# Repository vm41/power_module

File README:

-------------------------------------------------------
This is new branch c122017 created from the master branch
Migration of measure.py to more object oriented form.

DO NOT DELETE "2016_everything.zip"
That is not a backup!
----------------------------------
Documentations for selecting the hardware and instruments can be found in "doc"
Basic test scripts can be found in i2c-test

measure.py is the code to run on the drone, to measure motors currents, as well as 
receiving information from the agent, and recording them in log files.

constant.py is a configuration file imported in measure.py

tcp_client.py is a test code to run and act as the agent to send some 
commands to the measure.py manually.

graphs/
All graph related scripts, the ones in 2016 are not necessarily kept anymore, be careful.

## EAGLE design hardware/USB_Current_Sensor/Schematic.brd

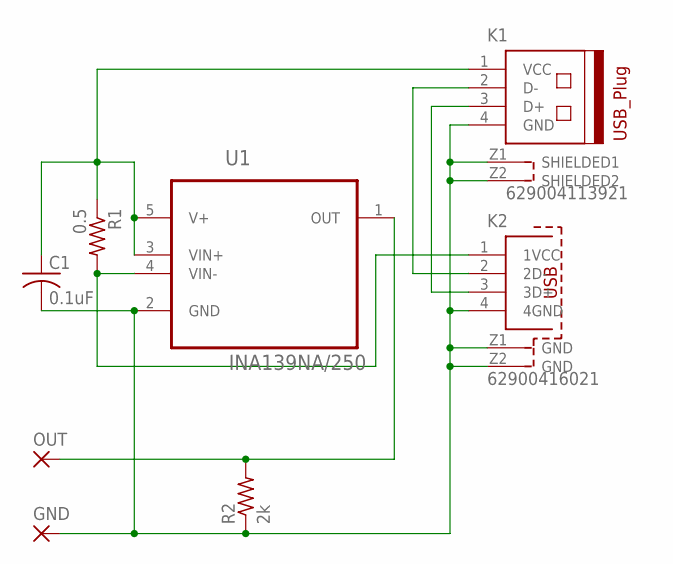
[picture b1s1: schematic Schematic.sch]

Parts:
C1: 0.1uF; C1808
GND: 2,54/1,0
K1: 629004113921
K2: 62900416021
OUT: 2,54/1,0
R1: 0.5; R1206
R2: 2k; R1206
U1: INA139NA/250; SOT95P280X145-5N

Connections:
unnamed: C1.2, GND.1, K1.4 (GND), K1.Z1 (SHIELDED1), K1.Z2 (SHIELDED2), K2.4 (4GND), K2.Z1 (GND), K2.Z2 (GND), R2.1, U1.2 (GND)
unnamed: K1.3 (D+), K2.3 (3D+)
unnamed: K1.2 (D-), K2.2 (2D-)
unnamed: C1.1, K1.1 (VCC), R1.1, U1.3 (VIN+), U1.5 (V+)
unnamed: OUT.1, R2.2, U1.1 (OUT)
unnamed: K2.1 (1VCC), R1.2, U1.4 (VIN-)

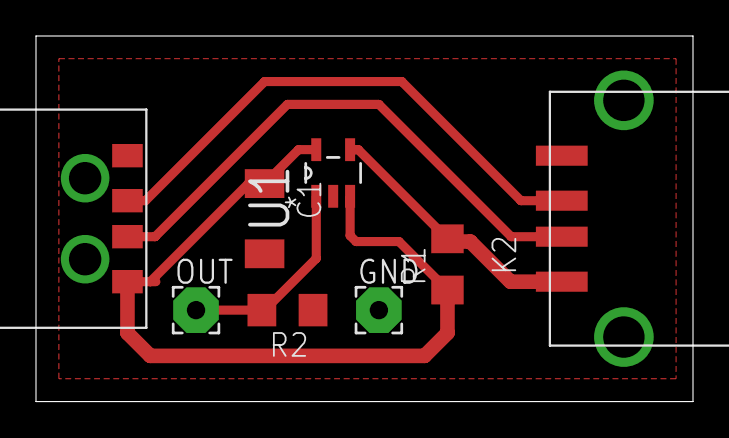
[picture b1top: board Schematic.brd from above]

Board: 2 copper layers, 36.5 x 20.3 mm, 8 parts (0 on the bottom side), 6 nets.

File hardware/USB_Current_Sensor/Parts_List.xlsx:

Number of Boards: |  | 3
Component |  | Quantity (per Board) |  | Quantity (Total) |  | Part Number |  | Price (per Part) |  | Price (Total) | Part Link
Current transducer |  | 1 |  | 3 |  | INA139NA/250 |  | 2 |  | 6 | digikey
0.5ohm resistor |  | 1 |  | 3 |  | CSR1206FTR500 |  | 0.42 |  | 1.26 | digikey
2kohm resistor |  | 1 |  | 3 |  | TNPW12062K00BEEA |  | 0.72 |  | 2.16 | digikey
0.1uF capacitor |  | 1 |  | 3 |  | VJ1808Y104KXCAT |  | 0.75 |  | 2.25 | digikey
USB A Male |  | 1 |  | 3 |  | "629004113921" |  | 2.21 |  | 6.63 | digikey
USB A Female |  | 1 |  | 3 |  | "62900416021" |  | 2.36 |  | 7.08 | digikey
 |  |  |  |  |  |  |  | Price (per Board) |  | Price (Total boards)
 |  |  |  |  |  |  |  | 8.4599999999999991 |  | 25.379999999999995

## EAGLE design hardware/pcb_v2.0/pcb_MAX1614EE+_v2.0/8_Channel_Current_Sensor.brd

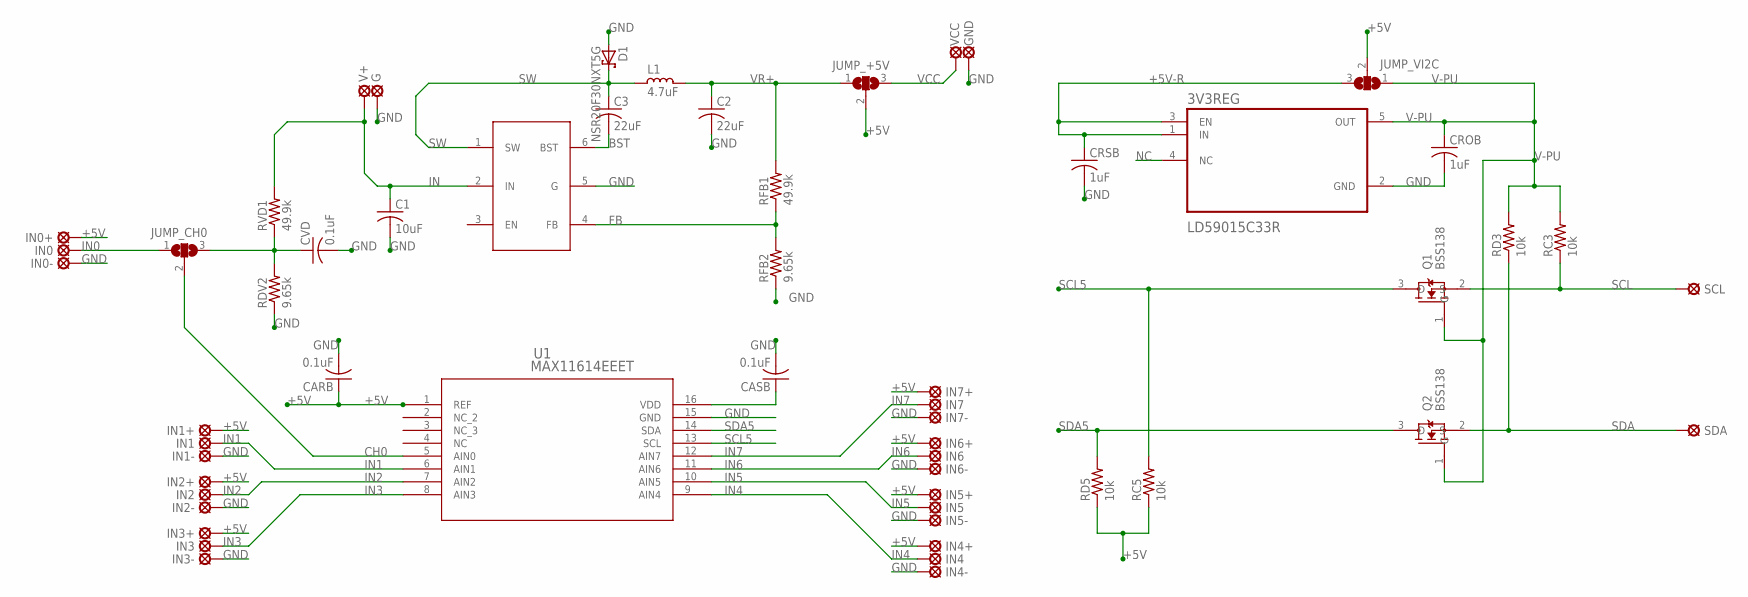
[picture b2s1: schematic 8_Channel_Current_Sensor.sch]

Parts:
3V3REG: LD59015C33R; SOT65P210X110-5N
5VBUCK: ACT4088US-T; SOT236
C1: 10uF; C0603K
C2, C3: 22uF; C0603K
CARB: 0.1uF; C0603
CASB: 0.1uF; C0603
CROB: 1uF; C0603
CRSB: 1uF; C0603
CVD: 0.1uF; C0603K
D1: NSR20F30NXT5G; C0603K
G: LSP10
GND: LSP10
IN0, IN0+, IN0-, IN1, IN1+, IN1-, IN2, IN2+, IN2-, IN3, IN3+, IN3-, IN4, IN4+, IN4-, IN5, IN5+, IN5-, IN6, IN6+, IN6-, IN7, IN7+, IN7-: LSP10
JUMP_+5V: SJ2W; SJ_2
JUMP_CH0: SJ2W; SJ_2
JUMP_VI2C: SJ2W; SJ_2
L1: 4.7uF; PM1008
Q1, Q2: BSS138; SOT95P240X120-3N
RC3, RC5: 10k; R0603
RD3, RD5: 10k; R0603
RDV2: 9.65k; R0603
RFB1: 49.9k; R0603
RFB2: 9.65k; R0603
RVD1: 49.9k; R0603
SCL: LSP10
SDA: LSP10
U1: MAX11614EEET; 21-0055H_16
V+: LSP10
VCC: LSP10

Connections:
+5V: CARB.1, CASB.1, IN0+.MP, IN1+.MP, IN2+.MP, IN3+.MP, IN4+.MP, IN5+.MP, IN6+.MP, IN7+.MP, JUMP_+5V.2, JUMP_VI2C.2, RC5.1, RD5.1, U1.1 (REF), U1.16 (VDD)
+5V-R: 3V3REG.1 (IN), 3V3REG.3 (EN), CRSB.1, JUMP_VI2C.3
BST: 5VBUCK.6 (BST), C3.2
CH0: JUMP_CH0.2, U1.5 (AIN0)
FB: 5VBUCK.4 (FB), RFB1.1, RFB2.2
GND: 3V3REG.2 (GND), 5VBUCK.5 (G), C1.2, C2.2, CARB.2, CASB.2, CROB.2, CRSB.2, CVD.2, D1.1 (A), G.MP, GND.MP, IN0-.MP, IN1-.MP, IN2-.MP, IN3-.MP, IN4-.MP, IN5-.MP, IN6-.MP, IN7-.MP, RDV2.1, RFB2.1, U1.15 (GND)
IN: 5VBUCK.2 (IN), C1.1, RVD1.2, V+.MP
IN0: IN0.MP, JUMP_CH0.1
IN1: IN1.MP, U1.6 (AIN1)
IN2: IN2.MP, U1.7 (AIN2)
IN3: IN3.MP, U1.8 (AIN3)
IN4: IN4.MP, U1.9 (AIN4)
IN5: IN5.MP, U1.10 (AIN5)
IN6: IN6.MP, U1.11 (AIN6)
IN7: IN7.MP, U1.12 (AIN7)
NC: 3V3REG.4 (NC)
SCL: Q1.2 (S), RC3.1, SCL.MP
SCL5: Q1.3 (D), RC5.2, U1.13 (SCL)
SDA: Q2.2 (S), RD3.1, SDA.MP
SDA5: Q2.3 (D), RD5.2, U1.14 (SDA)
SW: 5VBUCK.1 (SW), C3.1, D1.2 (C), L1.2
V-PU: 3V3REG.5 (OUT), CROB.1, JUMP_VI2C.1, Q1.1 (G), Q2.1 (G), RC3.2, RD3.2
VCC: JUMP_+5V.3, VCC.MP
VD: CVD.1, JUMP_CH0.3, RDV2.2, RVD1.1
VR+: C2.1, JUMP_+5V.1, L1.1, RFB1.2

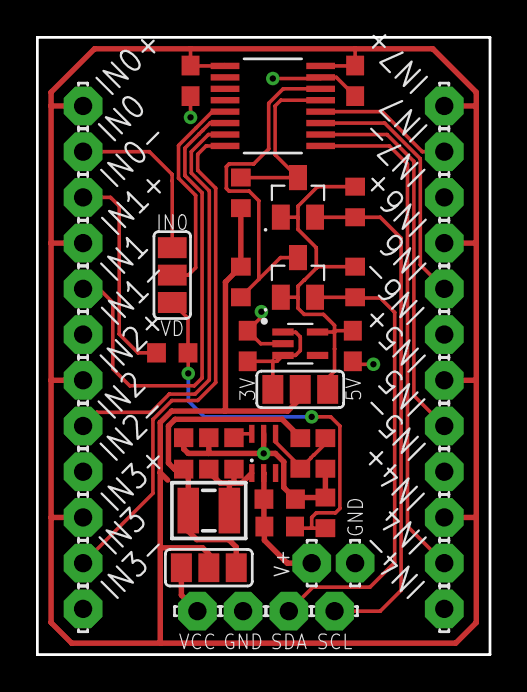
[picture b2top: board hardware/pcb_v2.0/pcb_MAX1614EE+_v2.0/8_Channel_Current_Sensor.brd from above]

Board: 2 copper layers, 25.1 x 34.3 mm, 56 parts (0 on the bottom side), 24 nets.

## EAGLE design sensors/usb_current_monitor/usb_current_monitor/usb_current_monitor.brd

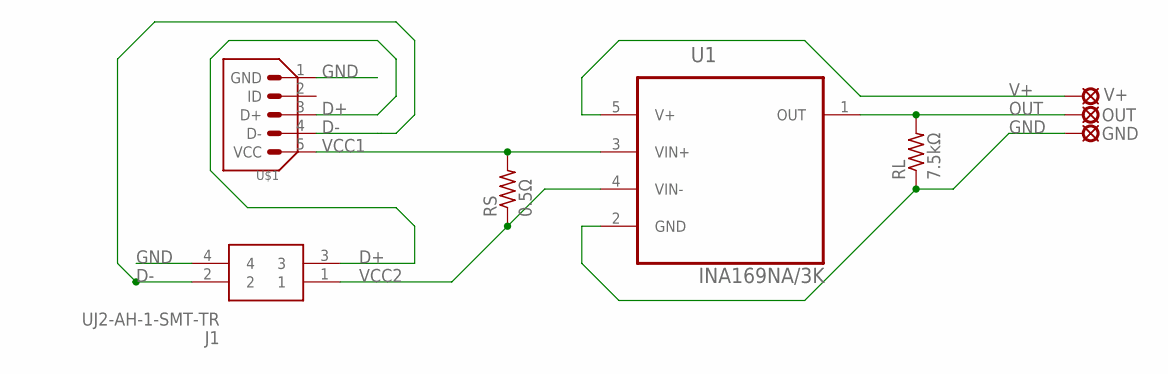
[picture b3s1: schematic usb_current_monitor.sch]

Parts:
GND: LSP10
J1: UJ2-AH-1-SMT-TR
OUT: LSP10
RL: 7.5kΩ; R0603
RS: 0.5Ω; R0603
U1: INA169NA/3K; SOT95P280X145-5N
U$1: ZX62R-B-5P
V+: LSP10

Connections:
D+: J1.3, U$1.3 (D+)
D-: J1.2, U$1.4 (D-)
GND: GND.MP, J1.4, RL.1, U1.2 (GND), U$1.1 (GND)
OUT: OUT.MP, RL.2, U1.1 (OUT)
V+: U1.5 (V+), V+.MP
VCC1: RS.2, U1.3 (VIN+), U$1.5 (VCC)
VCC2: J1.1, RS.1, U1.4 (VIN-)

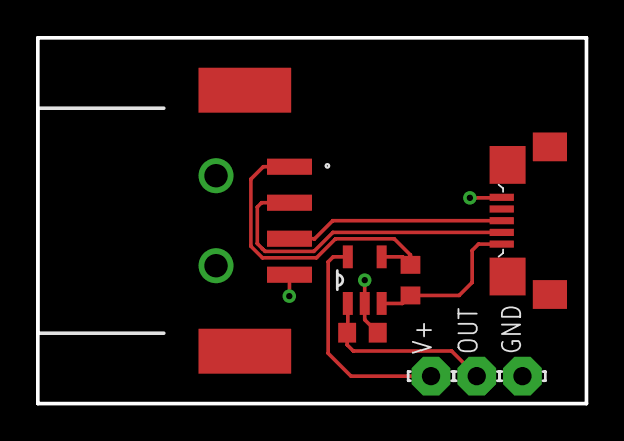
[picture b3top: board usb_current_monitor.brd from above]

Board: 2 copper layers, 30.5 x 20.3 mm, 8 parts (0 on the bottom side), 7 nets.

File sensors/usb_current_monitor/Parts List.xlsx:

No of Boards (mult of 3) | 3
Part | Part No | Quanity | Ext Quantity | Cost | Ext. Cost | Link
Shunt Monitor | INA169NA/3K | 1 | 3 | 2.21 | 6.63 | mouser
Micro USB Connector | ZX62R-B-5P(30) | 1 | 3 | 0.93 | 2.79 | mouser
USB Type A Connector | UJ2-AH-1-SMT-TR | 1 | 3 | 1.1599999999999999 | 3.4799999999999995 | mouser
0.5Ω 0805 Shunt Resistor | LRCS0805-0R5FT5 | 1 | 3 | 0.17 | 0.51 | mouser
7.5kΩ 0805 Load Resistor | ERJ-PB6B7501V | 1 | 3 | 0.57999999999999996 | 1.7399999999999998 | mouser
Optional Headers - Ignore for now |  | 0 | 0 | 0 | 0
Signal Header Female | 505567-0371 | 0 | 0 | 0.73 | 0 | mouser
Signal Header Male | 505565-0301 | 0 | 0 | 0.25 | 0 | mouser
 |  |  | Total Cost: |  | 15.149999999999999

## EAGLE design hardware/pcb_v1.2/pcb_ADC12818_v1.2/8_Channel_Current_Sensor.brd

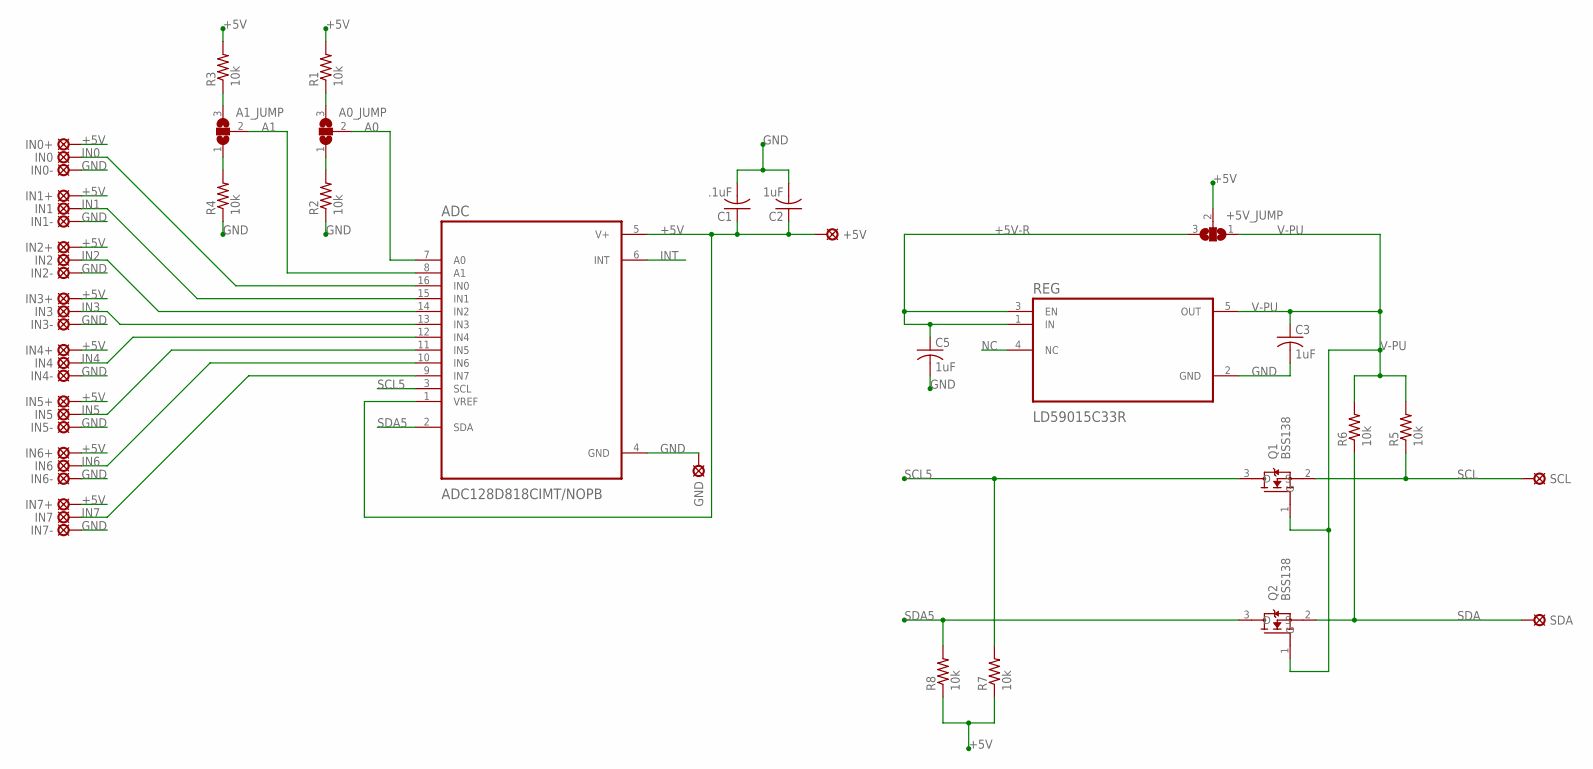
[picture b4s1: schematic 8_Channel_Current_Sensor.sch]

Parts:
+5V: LSP10
+5V_JUMP: SJ2W; SJ_2
A0_JUMP, A1_JUMP: SJ2W; SJ_2
ADC: ADC128D818CIMT/NOPB; SOP65P640X120-16N
C1: .1uF; C0603
C2, C3, C5: 1uF; C0603
GND: LSP10
IN0, IN0+, IN0-, IN1, IN1+, IN1-, IN2, IN2+, IN2-, IN3, IN3+, IN3-, IN4, IN4+, IN4-, IN5, IN5+, IN5-, IN6, IN6+, IN6-, IN7, IN7+, IN7-: LSP10
Q1, Q2: BSS138; SOT95P240X120-3N
R1, R2, R3, R4, R5, R6, R7, R8: 10k; R0603
REG: LD59015C33R; SOT65P210X110-5N
SCL: LSP10
SDA: LSP10

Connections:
+5V: +5V.MP, +5V_JUMP.2, ADC.1 (VREF), ADC.5 (V+), C1.1, C2.1, IN0+.MP, IN1+.MP, IN2+.MP, IN3+.MP, IN4+.MP, IN5+.MP, IN6+.MP, IN7+.MP, R1.2, R3.2, R7.1, R8.1
+5V-R: +5V_JUMP.3, C5.1, REG.1 (IN), REG.3 (EN)
A0: A0_JUMP.2, ADC.7 (A0)
A1: A1_JUMP.2, ADC.8 (A1)
GND: ADC.4 (GND), C1.2, C2.2, C3.2, C5.2, GND.MP, IN0-.MP, IN1-.MP, IN2-.MP, IN3-.MP, IN4-.MP, IN5-.MP, IN6-.MP, IN7-.MP, R2.1, R4.1, REG.2 (GND)
IN0: ADC.16 (IN0), IN0.MP
IN1: ADC.15 (IN1), IN1.MP
IN2: ADC.14 (IN2), IN2.MP
IN3: ADC.13 (IN3), IN3.MP
IN4: ADC.12 (IN4), IN4.MP
IN5: ADC.11 (IN5), IN5.MP
IN6: ADC.10 (IN6), IN6.MP
IN7: ADC.9 (IN7), IN7.MP
INT: ADC.6 (INT)
unnamed: A1_JUMP.3, R3.1
unnamed: A1_JUMP.1, R4.2
unnamed: A0_JUMP.1, R2.2
unnamed: A0_JUMP.3, R1.1
NC: REG.4 (NC)
SCL: Q1.2 (S), R5.1, SCL.MP
SCL5: ADC.3 (SCL), Q1.3 (D), R7.2
SDA: Q2.2 (S), R6.1, SDA.MP
SDA5: ADC.2 (SDA), Q2.3 (D), R8.2
V-PU: +5V_JUMP.1, C3.1, Q1.1 (G), Q2.1 (G), R5.2, R6.2, REG.5 (OUT)

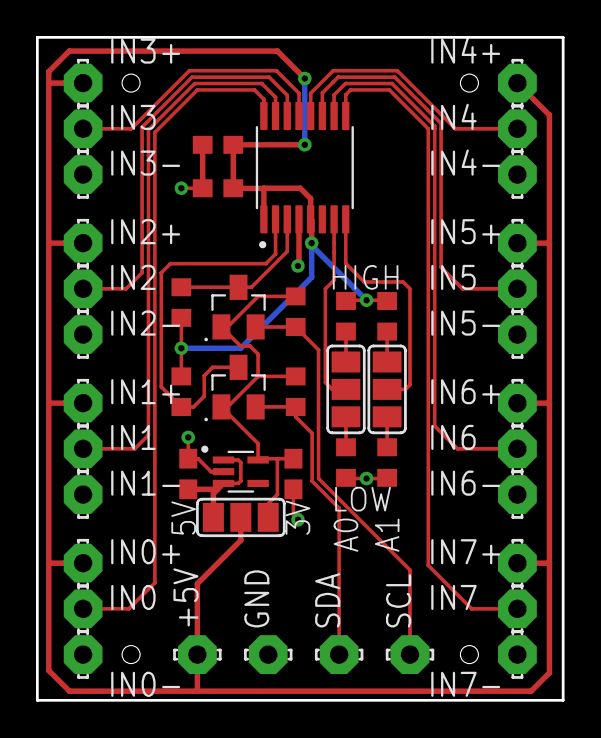
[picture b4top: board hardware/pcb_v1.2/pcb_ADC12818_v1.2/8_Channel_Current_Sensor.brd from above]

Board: 2 copper layers, 29.2 x 36.8 mm, 47 parts (0 on the bottom side), 22 nets.

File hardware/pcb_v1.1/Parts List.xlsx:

Number of Boards | 3 | Multiples of 3 only
Component | Quantity | Extd Quantity | Type/Value | Part Number | Price | Extended Price | Link
ADC | 1 | 3 |  | ADC128D818CIMTX/NOPB | 4.55 | 13.649999999999999 | mouser
Voltage Regulator | 1 | 3 | linear regulator | LD59015C33R | 0.67 | 2.0100000000000002 | mouser
Switch | 1 | 3 | SPDT | EG1218 | 0.56000000000000005 | 1.6800000000000002 | mouser
MOSFET | 2 | 6 | N Ch Enhancement | BSS138N H6327 | 0.28999999999999998 | 1.7399999999999998 | mouser
Resistor | 8 | 24 | 10k | AC0603FR-0710KL | 1.6E-2 | 0.38400000000000001 | mouser
Capacitor | 1 | 3 | 1uF electrolytic or tantalum | F981E105MMA | 0.65 | 1.9500000000000002 | mouser
Capacitor | 1 | 3 | .1uF ceramic | VJ0603Y104JXQPW1BC | 0.1 | 0.30000000000000004 | mouser
Capacitor | 2 | 6 | 1uF cermic | VJ0603G105KXYCW1BC | 0.1 | 0.60000000000000009 | mouser
Board | 1 | 3 |  |  | 3.0666666666665998 | 9.1999999999998003 | oshpark
 |  |  |  | Total - Parts |  | 31.5139999999998
Assembly Items
Solder Wick | 1 | 1 | copper braid |  | 3.29 | 3.29 | amazon
Solder Paste | 1 | 1 | syringe |  | 9.99 | 9.99 | amazon
Squeegee | 1 | 1 |  |  | 3.65 | 3.65 | amazon
Stencil | 1 | 1 | 5 mil film, standard 1.25 in borders |  | 6.96 | 6.96 | oshstencils
Items we probably have
Tweezers |  |  | Anything with a fine point |  |  |  | amazon
Scotch Tape |  |  | For holding boards in place
Paper Towels |  |  | For cleanup
 |  |  |  | Total Price |  | 55.403999999999797

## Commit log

2018-04-11 Migrating to new repo, squash all commits up to Fall 2017.
2018-04-11 measure2.py converted into class format
2018-04-11 updated the gitignore to igore the trial folder
2018-04-11 updated gitignore, ignoring the graphs-trials
2018-04-11 checked
2018-04-11 'stashing'
2018-04-11 added gitignore file, currently ignoring the current folder, contains dummy data
2018-04-11 stacking
2018-04-11 defined class constants and added more methods
2018-04-11 fixed one bug related to failure in calibration
2018-04-11 craeted tcp_client2.py in object oriented model
2018-04-11 configs changed
2018-04-11 updated gitignore
2018-04-11 ignorging .pyc files
2018-04-11 added class conversion file for the measure.py
2018-04-11 modified git ignore
2018-04-11 fixed the graph_bar_all script to show the total energies
2018-04-11 adding some files from summer. check constants.py
2018-04-11 mew schematic uploaded
2018-04-11 semi-ready
2018-04-11 added new sessions
2018-04-11 Added Eagle schematics, libraries and design material for ADC board
2018-04-11 Added hardware datasheets and unzipped redesign file
    Unzipped redesign folder and added datasheets for ADC and voltage regulator for reference
2018-04-11 updated PC-test
2018-04-11 pre liminary schematic for current sensor
2018-04-11 organazied completely, logs taken out, this is now only power_module regardless of the project
2018-04-11 added summary
2018-04-11 added new sensor datasheet and partial config
2018-04-13 Implemented object oriented approach to ADC reading
    Created a python file called "ADC128D818.py" which contains a class and all neccessary constants to create, initialize, and read from the ADC as its own object. The measure.py code was updated to uti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
2018-04-15 New PCB designs, reorganized files, removed clutter
    Added pcb v1.2 the final draft of the ADC12818 board.
    Added pcb v2.0 the new board boased on the MAX1614EE+ ADC
    Added datasheet for MAX ADC
    Renamed folders to have consistent naming scheme
    Removed unncessary tempoary files
2018-04-16 fixed a couple of bugs related to PI reading
2018-04-18 v2.5 of measure
2018-04-19 seached for bug, was able to take successful live readings, tested channel disabling, disabled all unused channels
2018-04-20 removed old measure code and renamed the new one
2018-04-25 Bug fixes
    Removed adc.stop() from measure.py and moved it into the initializtion function of the adc class
2018-04-25 Bug fixes
    small changed to unsused class
2018-04-26 restructured a bit, added feature to select channels to measure, added voltage divider channel to measure battery, has not yet been tested on hardware
2018-04-29 added pcb designs for usb current monitor
    Added datasheets, libraries, part list, and design for a custom cirucut board which provides passthrough USB power and monitors the current being drawn by the attached device
2018-04-29 error correction on usb current monitor board
    Flipped VIN+ and VIN- on the current sensor to conform with correct direction of current flow
2018-05-08 Finished v2 of ADC board
    Completed changes to ADC board and parts list.
    Changes:
    -Added header for voltage directly from the battery
    -Added voltage divider to measure battery voltage
    -Added buck converter to make clean 5V from battery voltage
    -Switched to more accurate MAX1614 ADC
2018-05-22 code restructured to prevent logging for disabled channels
2018-06-05 added channels' output on the terminal
2018-06-05 code optimization
2018-06-06 renamed v2.5 to v3, was annoying :D
2018-06-07 bug fixes
2018-06-07 Added Gerber Files for ADC board v2
    Generated Gerber files using the Oshpark CAM file I created. Gerber files can now be sent for manufacture of boards and stencils
2018-06-08 added uncalibration option
2018-06-08 fixed random in PC_SIMULATE_DATA mode
2018-06-11 this commit is tuned for UB-ANC drones, some modifications has been made to constants.
2018-06-12 fixed syntax. flushing take ~30 ms, maybe it should not be explicitly asked for.
2018-06-12 The output flushing was getting clogged, changed it to one write command only, and removed flush syntax. Furthermore, two threads had a clogging issue, losing TCP request timings, fixed it by force y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
2018-06-12 time formatting in dump
2018-06-19 added graph files for current sensor and voltage sensor
2018-06-20 fixed a bug in logger module, added a preprocessing script, modified graph script for UB-ANC experiments
2018-06-21 updated git ignore to exclude current folder in graphs
2018-06-26 dumping calibration values, added read_bias to the ADC, removing extra prints
2018-07-10 updated measure so it stops measurement thread upon TCP disconnection
2018-07-19 removed old/irrelevant plot files
2018-07-19 one plot_all.py file to rule them all! As the name suggests, this had been created to contain all required for usual plottings.
2018-07-19 MAJOR COMMIT. introduced channel-motor mapping, adde hover setup, and combined all into TARGET_SETUP, added flag for STEADY DETECTION, added PATH graphing and animation, introduced LAN/LON reference,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
2018-07-19 updated constant.py to include EARTH radius, and reference LAT, LON
2018-07-19 added SENSOR_PURPOSE mapping
2018-07-26 modified graph script to graph/consider only between two EVENTs, enable WAIT_FOR_MEASURE_FLAG
2018-09-10 added a wait every 100 reading set, in order to empty TCP buffer. sleep(0) may have not worked properly. Also introduced corrupt packet detection and concatination with next packet. ignoring half pac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
2018-09-10 extracting time from info messages themselves rather thatn recording timestamps. also added INITIAL_SETUP feature so that one can choose one or few SETUPs with correct labeling
2018-10-10 fixed a typo for uncalibrating the battery voltage channel 4
2018-10-10 tcp_client was case sensitive, now it accepts lower case comands too
2018-10-10 added TCP_CLIENT_DEPENDENCY option, for better handling session disconnections. Updated TCP client interface, also fixing support for markers
2019-07-06 Zipped Gerber files for PCB manufacturing
2019-07-06 Gerber Files
2019-07-11 PCB design for usb current monitor
2019-08-16 Modified the power_module to be used with erle-copter -Changed ADC address from "LOW_LOW" to "MID_MID" -Changed the channel sensor map to reflect the channels used on the ADC -Added the shunt convers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
2019-08-28 updated the conversion and constants files
2019-10-06 moving back to UB-ANC platform, adding extr channels for DEVICE measurements, introducing START_TIME and DURATION for graphing.
2019-10-09 reverted conversion of HALL sensor to simple scale. (remember to handle calibration/uncalibration in measrement). working on plot script, ongoing...
2019-10-09 Jerin fixed errors, and updated calibration for kinect experiment
2019-10-09 manual calibration added for device hall sensors (not tested yet)
2019-10-09 Added second hall sensor for barrel connector, fixed case where USB sensor reading would go above max voltage
2019-10-09 improved fonts in plot_all, and added start/duration

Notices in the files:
parts and their libraries:
Wurth_Elektronik_Electromechanic_Input-O: Copyright: Würth Elektronik
rc-master-smd: Copyright (C) 2007, Bob Starr
